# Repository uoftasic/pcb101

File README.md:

# PCB101 — PCB Design with KiCad

Design the boards a chip sits on: schematics, footprints from datasheets, layout, protection, fab outputs in CI, review, and a bring-up board for a team chip.

Part of the UofT ASIC Team education materials (`uoftasic`). The course is for both tracks, analog and digital, and comes after IC101 and IC102.
Course site: <https://uoftasic.com/pcb101/> · Education hub: <https://edu.uoftasic.com/>

Students draw in KiCad 10.0 installed on their own computers, 10.0.5 if they can get it ([Getting started](https://uoftasic.com/pcb101/guide/getting-started.html) says what to install). The labs' checks run in the official image `kicad/kicad:10.0.5`, pinned by digest in [`labs/common/kicad-image.txt`](labs/common/kicad-image.txt), and every ERC, DRC and parity count that a lab page shows comes from `kicad-cli` there. The site's 3D renders come from the same `kicad-cli` in `kicad/kicad:10.0.5-full`, which adds KiCad's 3D models of parts ([`scripts/screenshots/kicad/render-image.txt`](scripts/screenshots/kicad/render-image.txt)). Lab 05 also runs KiBot, for an interactive BOM and a design report, in KiBot's own image with KiCad 10.0.5, pinned in [`labs/common/kibot-image.txt`](labs/common/kibot-image.txt). A few checks don't use KiCad at all. The bring-up plan check (`labs/common/check_bringup.py`) is one of them, and it needs only Python. Unlike the analog and digital courses, PCB101 doesn't use the workbench that students set up in IC101.

## Quick start

You need Docker, git and Python 3. From a clone of this repo:

```bash
python3 labs/common/fetch_boards.py          # Tiny Tapeout's boards, at pinned commits, into labs/common/upstream/
labs/common/kicad.sh python3 labs/common/check_board.py labs/common/upstream/breakout-pcb/breakout-sky-qfn
```

The second command ends with `FAIL  erc.error: 10 (want 0)` and `FAIL  parity.warning: 37 (want 0)`, because in KiCad 10.0.5 Tiny Tapeout's SKY130 breakout has 10 ERC errors and 37 schematic parity warnings. [`labs/common/README.md`](labs/common/README.md) explains the output, the checker's rules, and how a lab uses them.

## Lab packages

| Path | What it is | Writeup |
|---|---|---|
| `labs/lab-01-open-a-board-you-didnt-design/` | the notes template for Tiny Tapeout's SKY130 breakout, and the check that compares a student's notes with the board | [Lab 01](https://uoftasic.com/pcb101/labs/lab-01-open-a-board-you-didnt-design-overview.html) |
| `labs/lab-02-a-footprint-from-a-datasheet/` | the RHL0024A drawing data, an empty footprint and symbol library, and the check that compares them with the student's own pad numbers | [Lab 02](https://uoftasic.com/pcb101/labs/lab-02-a-footprint-from-a-datasheet-overview.html) |
| `labs/lab-03-a-pmod-for-one-projects-pins/` | the board template a student copies into their own repository, and the reference SimProc Pmod | [Lab 03](https://uoftasic.com/pcb101/labs/lab-03-a-pmod-for-one-projects-pins-overview.html) |
| `labs/lab-04-protect-and-plan/` | the `BRINGUP.md` template, and the reference board with its protection and plan | [Lab 04](https://uoftasic.com/pcb101/labs/lab-04-protect-and-plan-overview.html) |
| `labs/lab-05-fab-outputs-in-ci/` | the starter workflow, build script and KiBot configuration, and the check that runs the build and KiBot in a student's repository, then looks at what they made and what git tracks | [Lab 05](https://uoftasic.com/pcb101/labs/lab-05-fab-outputs-in-ci-overview.html) |
| `labs/lab-06-review-a-seeded-board/` | the seeded board, the `REVIEW.md` and `QUOTE.md` templates, and their check | [Lab 06](https://uoftasic.com/pcb101/labs/lab-06-review-a-seeded-board-overview.html) |
| `labs/capstone-a-board-for-a-team-chip/` | the `DESIGN.md` template, the check for both briefs, and a reference board for each | [Capstone](https://uoftasic.com/pcb101/labs/capstone-a-board-for-a-team-chip-overview.html) |
| `labs/common/` | the pinned-KiCad and KiBot wrappers, the board checker, the Pmod and bring-up plan checks, and the script that fetches Tiny Tapeout's boards | used by every lab |

Reference solutions go in each package's `solutions/` folder. `.github/workflows/labs.yml` runs the board checker on every KiCad project there, in the pinned image, on every change to `labs/**` and once a week.

## Screenshots and figures

[`scripts/screenshots/kicad/`](scripts/screenshots/kicad/README.md) takes GUI screenshots of KiCad's editors under Xvfb in the pinned image, and makes 3D renders and SVG plots with `kicad-cli`. Images for the site go in `docs/assets/img/`. The guide pages' diagrams and plots are drawn by the scripts in [`scripts/figures/`](scripts/figures/), listed in [`scripts/README.md`](scripts/README.md).

## Docs

The course site is built with Quarto from `./docs`. `docs/_quarto.yml` holds the site, sidebar and navbar, and `docs/_quarto-pdf.yml` builds the whole course as one PDF. To preview it you need [Quarto](https://quarto.org/docs/get-started/) 1.11:

```bash
quarto preview docs                            # -> http://localhost:4200
quarto render docs --profile pdf --to typst    # whole course as one PDF in docs/_book/
```

| Path | On Pages? | Purpose |
|------|-----------|---------|
| `docs/` | Yes | The course site; `docs/index.md` is the home page and has the Course path |
| `docs/guide/` | Yes | Guide pages: reading only, no commands |
| `docs/labs/` | Yes | Lab writeups: every command a student runs, in numbered parts and steps |
| `labs/` | No | Lab packages, and the shared checks in `labs/common/` |
| `scripts/` | No | `check_site.py` (the link check for the rendered site), the KiCad screenshot tools, and the scripts that draw the site's figures |

GitHub Pages is set to Source: GitHub Actions. `.github/workflows/site.yml` renders the site and the course PDF, checks the rendered site's links and anchors with `scripts/check_site.py`, and deploys `docs/_site`.

This repo was created from [uoftasic/course-template](https://github.com/uoftasic/course-template). `TEMPLATE.md` and `scripts/init-template.py` are that template's bootstrap files and aren't part of the course.

## Contributing

See [CONTRIBUTING.md](CONTRIBUTING.md) and [AGENTS.md](AGENTS.md).

## License

[MIT](LICENSE). Copyright UofT ASIC Team / `uoftasic`. Tiny Tapeout's boards and libraries are fetched from their own repositories and keep their own licences, which [`labs/common/upstream.json`](labs/common/upstream.json) records.

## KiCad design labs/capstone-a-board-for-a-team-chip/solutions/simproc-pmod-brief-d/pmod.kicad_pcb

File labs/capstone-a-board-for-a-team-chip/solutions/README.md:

# Capstone references

Each folder is a whole board repository: the KiCad project, `DESIGN.md`, `BRINGUP.md`, and Lab 05's `ci/`, `.github/workflows/board.yml` and `.gitignore`. Nothing in either has been built or measured; every expected value is worked out from part values and the sources each `DESIGN.md` names.

| Folder | Brief | Board check in `kicad/kicad:10.0.5` | Capstone check |
|---|---|---|---|
| `simproc-pmod-brief-d/` | D: the SimProc Pmod | ERC 0; DRC 0 errors, 32 warnings (24 `silk_edge_clearance`, 6 `silk_over_copper`, 2 `silk_overlap`); 0 unconnected; 0 parity | `PASS  pmod, Brief D: 5 of 5 capstone checks ok` |
| `source-board-brief-a/` | A: a source for an0 on J13 | ERC 0; DRC 0 errors, 0 warnings; 0 unconnected; 0 parity | `PASS  source, Brief A: 8 of 8 capstone checks ok` |

## Brief D

Lab 04's reference board with two test points, written by [`../src/make_brief_d.py`](../src/make_brief_d.py):

| Part | Footprint | Net | Where (mm) |
|---|---|---|---|
| TP3 | `TestPoint:TestPoint_Pad_D1.5mm` | `UART_RX` (`ui[0]`, between J1 and R1) | (117.3, 60.0), on a track from (114.70, 59.0) |
| TP4 | same | `DONGLE_RXD` (`uo[0]`, between R2 and J4) | (119.0, 73.2), on a track from the via under R2 at (119.0, 71.08) |

TP3 sits below the Pmod connectors' courtyards, which reach down to Y 58.2 mm. Its reference is above it and 1 mm to the right, clear of R1's, which is above R1. TP4's reference is moved under it, clear of TP2's. `BRINGUP.md` is Lab 04's, with steps 6 and 7 read at TP4 and TP3. The two `silk_overlap` warnings are Lab 04's, R3's reference over SW1's outline.

## Brief A

A 50 × 30 mm board, written by [`../src/make_brief_a.py`](../src/make_brief_a.py):

| Part | Value | Footprint | Nets | Where (mm, degrees) |
|---|---|---|---|---|
| J1 | socket for J13 | `Connector_PinSocket_2.54mm:PinSocket_2x16_P2.54mm_Vertical`, on the bottom | GND on 1, 6, 9, 14, 17, 22, 25, 30, 31; +3V3 on 32; AN0 on 4; the rest open | pad 1 at (106, 76), flipped, 270° |
| RV1 | 1 kΩ | `Potentiometer_THT:Potentiometer_Bourns_3296W_Vertical` | +3V3, SET, GND | (134, 58), 0° |
| R1 | 1 kΩ | `Resistor_SMD:R_0805_2012Metric_Pad1.20x1.40mm_HandSolder` | SET to AN0 | (122, 62), 180° |
| C1 | 10 nF | `Capacitor_SMD:C_0805_2012Metric_Pad1.18x1.45mm_HandSolder` | AN0 to GND | (112, 66), 270° |
| TP1, TP2 | test points | `TestPoint:TestPoint_Pad_D1.5mm` | SET, AN0 | (131.46, 64.5), (116, 64.5) |

Of the eight ways to place J1 (four angles, either side), only flipped and turned 270° puts its 32 pads over J13's, pad for pad, seen from above; the generator compares the two patterns against the fetched demo board and stops if they differ. `DESIGN.md` assumes a sample rate of 400 kS/s for the droop in its decision 5, and says so; CrossWalk's documentation doesn't give one yet.

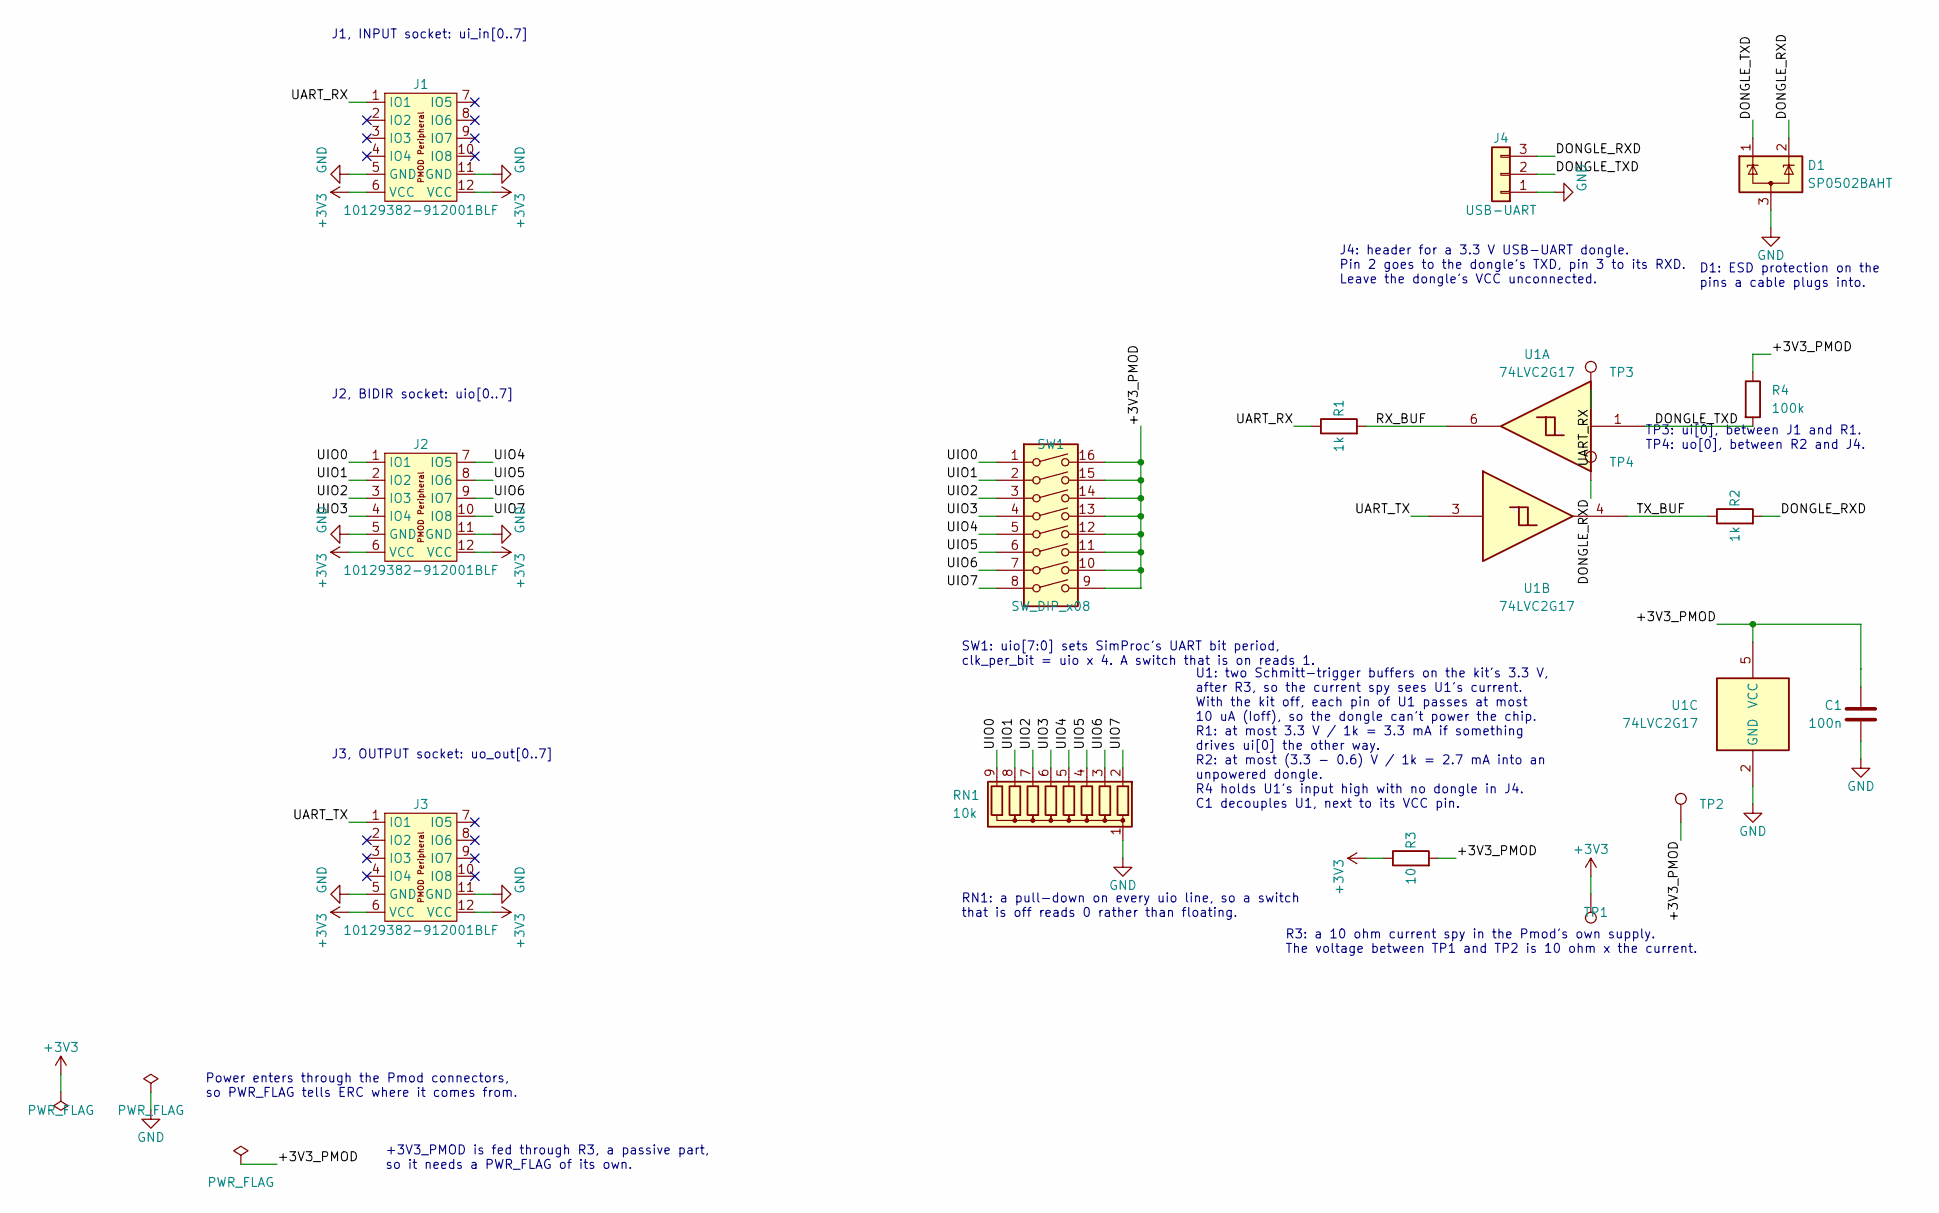
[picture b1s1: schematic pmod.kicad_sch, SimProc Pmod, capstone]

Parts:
C1: 100n; C_0805_2012Metric_Pad1.18x1.45mm_HandSolder
D1: SP0502BAHT; SOT-23
J1, J2, J3: 10129382-912001BLF; PinHeader_2x06_P2.54mm_PMODPeriph2B; LCSC Part C492434
J4: USB-UART; PinHeader_1x03_P2.54mm_Vertical
R1, R2: 1k; R_0805_2012Metric_Pad1.20x1.40mm_HandSolder
R3: 10; R_0805_2012Metric_Pad1.20x1.40mm_HandSolder
R4: 100k; R_0805_2012Metric_Pad1.20x1.40mm_HandSolder
RN1: 10k; R_Array_SIP9
SW1: SW_DIP_x08; SW_DIP_SPSTx08_Slide_9.78x22.5mm_W7.62mm_P2.54mm
TP1, TP2, TP3, TP4: TestPoint; TestPoint_Pad_D1.5mm
U1: 74LVC2G17; SOT-23-6

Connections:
+3V3: J1.6 (VCC), J1.12 (VCC), J2.6 (VCC), J2.12 (VCC), J3.6 (VCC), J3.12 (VCC), R3.1, TP1.1
/+3V3_PMOD: C1.1, R3.2, R4.1, SW1.9, SW1.10, SW1.11, SW1.12, SW1.13, SW1.14, SW1.15, SW1.16, TP2.1, U1.5 (VCC)
/DONGLE_RXD: D1.2 (K), J4.3, R2.2, TP4.1
/DONGLE_TXD: D1.1 (K), J4.2, R4.2, U1.1
/RX_BUF: R1.2, U1.6
/TX_BUF: R2.1, U1.4
/UART_RX: J1.1 (IO1), R1.1, TP3.1
/UART_TX: J3.1 (IO1), U1.3
/UIO0: J2.1 (IO1), RN1.9 (R8), SW1.1
/UIO1: J2.2 (IO2), RN1.8 (R7), SW1.2
/UIO2: J2.3 (IO3), RN1.7 (R6), SW1.3
/UIO3: J2.4 (IO4), RN1.6 (R5), SW1.4
/UIO4: J2.7 (IO5), RN1.5 (R4), SW1.5
/UIO5: J2.8 (IO6), RN1.4 (R3), SW1.6
/UIO6: J2.9 (IO7), RN1.3 (R2), SW1.7
/UIO7: J2.10 (IO8), RN1.2 (R1), SW1.8
GND: C1.2, D1.3 (A), J1.5 (GND), J1.11 (GND), J2.5 (GND), J2.11 (GND), J3.5 (GND), J3.11 (GND), J4.1, RN1.1 (common), U1.2 (GND)

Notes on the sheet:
R3: a 10 ohm current spy in the Pmod's own supply. The voltage between TP1 and TP2 is 10 ohm x the current.
J2, BIDIR socket: uio[0..7]
J1, INPUT socket: ui_in[0..7]
D1: ESD protection on the pins a cable plugs into.
J3, OUTPUT socket: uo_out[0..7]
TP3: ui[0], between J1 and R1. TP4: uo[0], between R2 and J4.
SW1: uio[7:0] sets SimProc's UART bit period, clk_per_bit = uio x 4. A switch that is on reads 1.
J4: header for a 3.3 V USB-UART dongle. Pin 2 goes to the dongle's TXD, pin 3 to its RXD. Leave the dongle's VCC unconnected.
U1: two Schmitt-trigger buffers on the kit's 3.3 V, after R3, so the current spy sees U1's current. With the kit off, each pin of U1 passes at most 10 uA (Ioff), so the dongle can't power the chip. R1: at most 3.3 V / 1k = 3.3 mA if something drives ui[0] the other way. R2: at most (3.3 - 0.6) V / 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
+3V3_PMOD is fed through R3, a passive part, so it needs a PWR_FLAG of its own.
RN1: a pull-down on every uio line, so a switch that is off reads 0 rather than floating.
Power enters through the Pmod connectors, so PWR_FLAG tells ERC where it comes from.

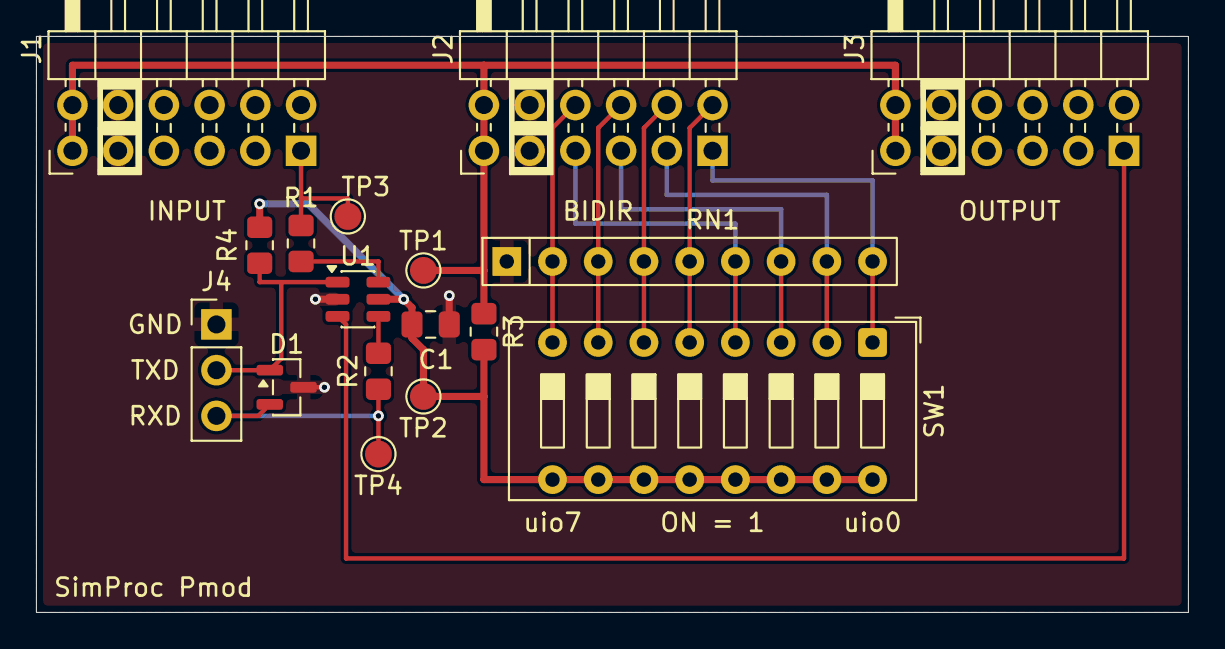
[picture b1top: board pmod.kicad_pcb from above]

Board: 2 copper layers, 64.0 x 32.0 mm, 17 parts (0 on the bottom side), 17 nets.

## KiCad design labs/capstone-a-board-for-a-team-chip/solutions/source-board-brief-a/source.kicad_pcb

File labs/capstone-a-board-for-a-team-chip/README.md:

# Capstone: A board for a team chip

Writeup: [`docs/labs/capstone-a-board-for-a-team-chip-overview.md`](../../docs/labs/capstone-a-board-for-a-team-chip-overview.md)
· live: <https://uoftasic.com/pcb101/labs/capstone-a-board-for-a-team-chip-overview.html>

You take one board to an orderable state in a repository of your own, under one of two briefs: D, a bring-up Pmod for a digital project, or A, a source board for one analog pin on the demo board's analog header J13. Check it with:

```bash
cd ~/simproc-pmod                                                     # your board repository
cp ~/pcb101/labs/capstone-a-board-for-a-team-chip/DESIGN.md .          # once
~/pcb101/labs/capstone-a-board-for-a-team-chip/check.sh --brief D      # or --brief A; --pins FILE for Brief D
```

`check.sh --brief D|A [--pins FILE]` runs [`src/check_capstone.py`](src/check_capstone.py) in the course's pinned KiCad image. It prints one row per check and a last line, `PASS` or `FAIL`. Exit status 0 is PASS, 1 FAIL, 2 couldn't run.

| Row | Brief | Passes when |
|---|---|---|
| ci | both | Lab 05's check passes: `ci/build.sh` passes the board check, builds every output, and leaves nothing untracked |
| design | both | `DESIGN.md` has its four sections filled in and no TODO, at least 3 numbered requirements and 3 numbered decisions, every decision a value with its unit and a `Meets:` line, and every requirement met |
| history | both | at least 2 commits change a `.kicad_sch` or `.kicad_pcb` |
| pmod | D | Lab 04's check passes (`check_pmod.py --protect --bringup BRINGUP.md`, with `--pins` if given): on each line that crosses from another supply, a buffer and a resistor, or a dual-supply translator such as the SN74LVC1T45 for a part at another voltage |
| test points | D | every non-GND pin of a connector other than the Pmods has a test point on its net, or further along its line to the Pmod pin: past a series resistor, or through a buffer or a translator from the Lab 04 check's lists, but not on GND or the sockets' 3.3 V on either side of the current-sense resistor, so the far side of a pull-up doesn't count. A connector pin that feeds a translator's VCCB carries the other side's supply, not a signal, and needs no test point |
| connector | A | one `Conn_02x16` symbol, with pins 1, 6, 9, 14, 17, 22, 25, 30 and 31 on GND and pin 32 on a 3.3 V net or open, as J13 has them |
| pin | A | exactly one of J13's twelve analog lines connected (pins 4, 5, 7, 10, 12, 13, 20, 21, 23, 26, 28, 29), and none of the eight that are ground on the SKY130 breakout |
| filter | A | that pin's net has a two-pin capacitor to GND and a two-pin resistor to a source net |
| test points | A | a test point on the pin's net and on the source net |
| bringup | A | `BRINGUP.md` passes [`labs/common/check_bringup.py`](../common/check_bringup.py) |

J13's pinout is from `TinyTapeout/tt-demo-pcb` at bbf3dd1, where J13 is a `PinHeader_2x16_P2.54mm_Vertical` marked DNP, and the analog pad behind each line comes from the SKY130 breakout's J1 at `breakout-pcb` 91a2bf1.

| Repository | Last line of the check |
|---|---|
| Lab 04's board, Lab 05's CI and `DESIGN.md` from here, in one commit | `FAIL  pmod, Brief D: 2 of 5 capstone checks ok` |
| `solutions/simproc-pmod-brief-d/` on top of that, as a second commit | `PASS  pmod, Brief D: 5 of 5 capstone checks ok` |
| `solutions/source-board-brief-a/`, in two commits | `PASS  source, Brief A: 8 of 8 capstone checks ok` |

## Files

| File | What it is |
|---|---|
| `check.sh` | the capstone's check, on your board repository |
| `DESIGN.md` | the design note's template |
| `solutions/` | a reference for each brief; see its README |
| `src/check_capstone.py` | the check itself |
| `src/make_brief_d.py` | writes the Brief D reference board: Lab 04's, with TP3 and TP4 |
| `src/make_brief_a.py` | writes the Brief A reference board, and checks its socket's pads against J13's when the demo board is fetched |
| `src/selftest.py` | repositories with known verdicts, for testing the check itself (4 of 4; in our run it took 116 s with the container limited to one CPU) |
| `results/` | local outputs; never committed |

```bash
labs/common/kicad.sh python3 labs/capstone-a-board-for-a-team-chip/src/make_brief_d.py labs/capstone-a-board-for-a-team-chip/solutions/simproc-pmod-brief-d
python3 labs/common/fetch_boards.py tt-demo-pcb
labs/common/kicad.sh python3 labs/capstone-a-board-for-a-team-chip/src/make_brief_a.py labs/capstone-a-board-for-a-team-chip/solutions/source-board-brief-a
labs/common/kicad.sh python3 labs/capstone-a-board-for-a-team-chip/src/selftest.py
```

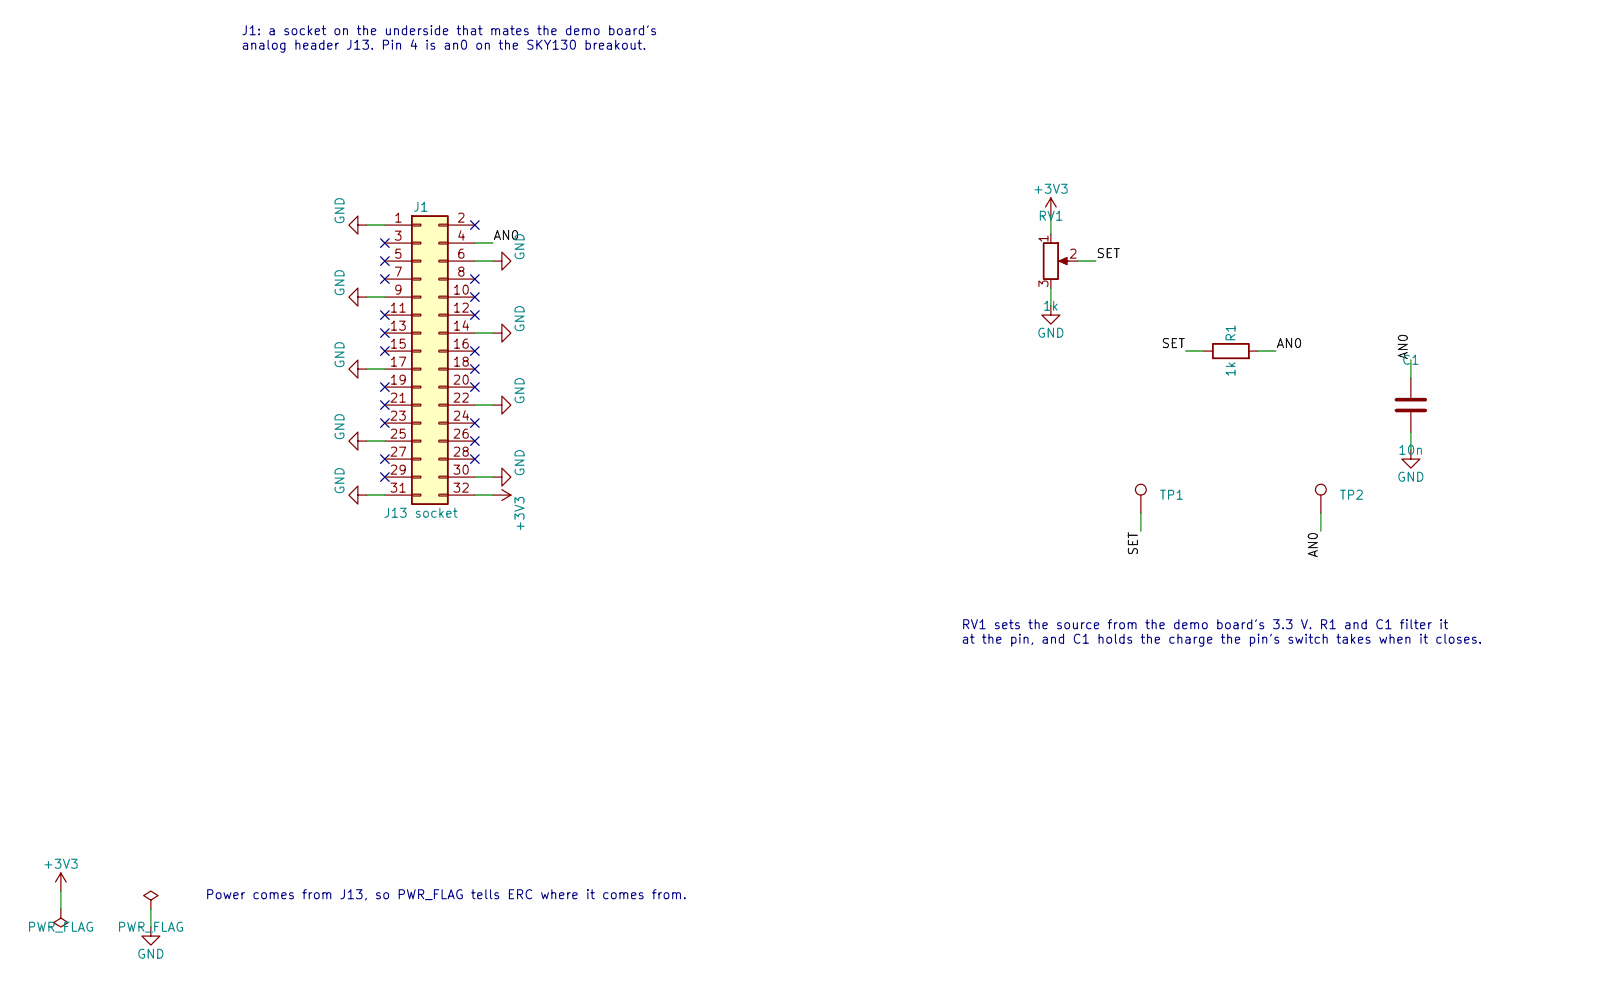
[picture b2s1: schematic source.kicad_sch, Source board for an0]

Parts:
C1: 10n; C_0805_2012Metric_Pad1.18x1.45mm_HandSolder
J1: J13 socket; PinSocket_2x16_P2.54mm_Vertical
R1: 1k; R_0805_2012Metric_Pad1.20x1.40mm_HandSolder
RV1: 1k; Potentiometer_Bourns_3296W_Vertical
TP1, TP2: TestPoint; TestPoint_Pad_D1.5mm

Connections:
+3V3: J1.32, RV1.1
/AN0: C1.1, J1.4, R1.2, TP2.1
/SET: R1.1, RV1.2, TP1.1
GND: C1.2, J1.1, J1.6, J1.9, J1.14, J1.17, J1.22, J1.25, J1.30, J1.31, RV1.3

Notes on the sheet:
J1: a socket on the underside that mates the demo board's analog header J13. Pin 4 is an0 on the SKY130 breakout.
RV1 sets the source from the demo board's 3.3 V. R1 and C1 filter it at the pin, and C1 holds the charge the pin's switch takes when it closes.
Power comes from J13, so PWR_FLAG tells ERC where it comes from.

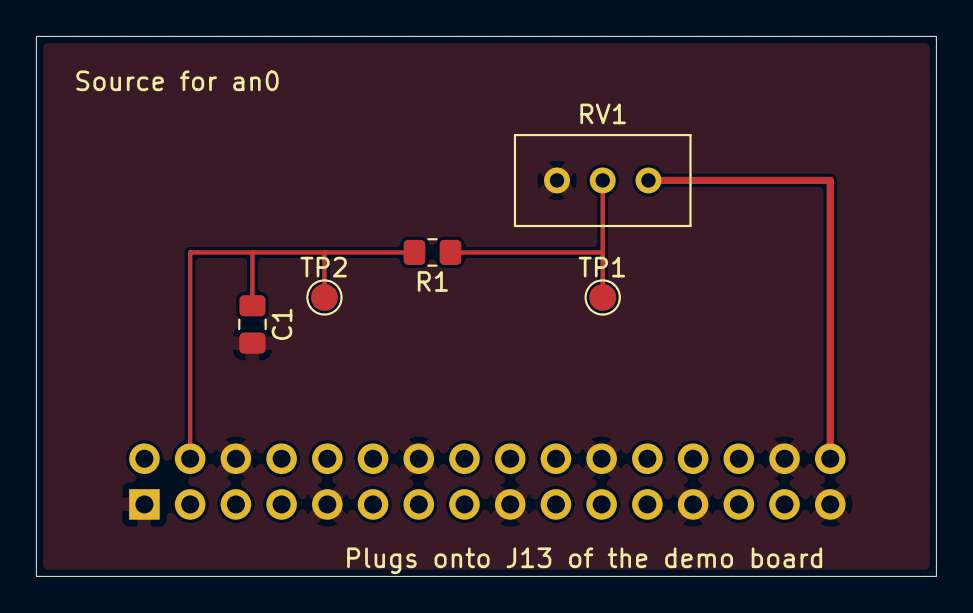
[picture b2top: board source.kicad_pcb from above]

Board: 2 copper layers, 50.0 x 30.0 mm, 6 parts (1 on the bottom side), 4 nets.
